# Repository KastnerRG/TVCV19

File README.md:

This software is Copyright © 2021 The Regents of the University of California. All Rights Reserved.

Permission to use, copy, modify, and distribute this software and its documentation for educational, research and non-profit purposes, without fee, and without a written agreement is hereby granted, provided that the above copyright notice, this paragraph and the following three paragraphs appear in all copies.

Permission to make commercial use of this software may be obtained by contacting:
Technology Transfer Office
9500 Gilman Drive, Mail Code 0910
University of California
La Jolla, CA 92093-0910
(858) 534-5815
invent@ucsd.edu

This software program and documentation are copyrighted by The Regents of the University of California. The software program and documentation are supplied "as is", without any accompanying services from The Regents. The Regents does not warrant that the operation of the program will be uninterrupted or error-free. The end-user understands that the program was developed for research purposes and is advised not to rely exclusively on the program for any reason.

IN NO EVENT SHALL THE UNIVERSITY OF CALIFORNIA BE LIABLE TO ANY PARTY FOR DIRECT, INDIRECT, SPECIAL, INCIDENTAL, OR CONSEQUENTIAL DAMAGES, INCLUDING LOST PROFITS, ARISING OUT OF THE USE OF THIS SOFTWARE AND ITS DOCUMENTATION, EVEN IF THE UNIVERSITY OF CALIFORNIA HAS BEEN ADVISED OF THE POSSIBILITY OF SUCH DAMAGE. THE UNIVERSITY OF CALIFORNIA SPECIFICALLY DISCLAIMS ANY WARRANTIES, INCLUDING, BUT NOT LIMITED TO, THE IMPLIED WARRANTIES OF MERCHANTABILITY AND FITNESS FOR A PARTICULAR PURPOSE. THE SOFTWARE PROVIDED HEREUNDER IS ON AN "AS IS" BASIS, AND THE UNIVERSITY OF CALIFORNIA HAS NO OBLIGATIONS TO PROVIDE MAINTENANCE, SUPPORT, UPDATES, ENHANCEMENTS, OR MODIFICATIONS.

# TVCV19

**MedECC** is an opensource telemedicine app to allow clinicians to better scale personnel resources.
Although hardware can be mass produced, clinician knowledge and experience cannot and this needs to be scaled out somehow.
Our platform aims to organize the heterogeneous hardware and manpower resources into a patient monitoring and decision making hierarchy.

If 10 COVID patients suddenly show up at a hospital with breathing difficulty, a misjudgement by the physician on who needs immediate intervention can be deadly. Our app allows caregivers to safely ration complex medical care to those who need it the most in order to save the most amount of lives.

This is how it works:

Traditionally, a bedside provider has to contact the physician via pager, a physician would then come to assess the patient at bedside, then put in orders before he/she can move onto the next patient.

The app provides instant access to a patient. A video feed along with real time patient data can be used by the supervising provider to assess a patient's condition. Once a decision is made, on the spot instructions can be given, or the supervisor can come prepared for a bedside procedure. This also means less exposure for doctors to infected patients, and less likely they’ll fall sick.

In cases where the supervising physician is overwhelmed or needs more complex help, the app allows quickly passing a patient to a specialist and ensures that cases are vetted before necessitating specialist attention.

You can learn more by browsing our [concept slides](https://docs.google.com/presentation/d/1jx_JJByAbFSXHXhZfbF9ar7q-Zx0MacvegpB00uDiNY/edit?usp=sharing) and listening to the accompanying [audio](https://www.uberconference.com/getmp3/AMIfv96b4tICKo7poclDD1wA3ljoQGVjX5lJ87UGyMusDsqpWrA9_SicAiTtTIgBCxpy7tUZsg8eZMD__9GbqGigc21ryxLr58KPmLOuIUcWgVltLQEmKRbjEPGKtYLqD_cy1Fx86Uls0aoCrx9p41Y52YWyEJF-Uw.mp3).

We are currently racing against the global novel coronavirus pandemic and could use a hand. 

If you want to contribute to the project, please fill out this [online form](https://docs.google.com/forms/d/e/1FAIpQLSf2osgKSobmYf0kSwzRrotV2hk5i8TjtZZdn5XptA1UjeIXVA/viewform)  and join our [slack channel](https://join.slack.com/t/scalablecv19solutions/shared_invite/zt-cxcbnbyu-yu4dxzaMjjnQvBGkQYVkxw) (#tv-cv19).

## How to Run
**Note:** If you have an old database created from the DB scripts, be sure to drop the DB before continuing.

### Setup the database for development
We use mySQL for our backend database.  The development instance uses a predetermined password.

To setup the database follow these steps:
1. Execute `ALTER USER 'root'@'localhost' IDENTIFIED BY 'Password1'` in mySQL
1. Execute `dotnet tool install --global dotnet-ef` to install the tools for Entity Framework.
1. Execute `dotnet ef database update` to create the database.

### Before running the C# Code
1. Navigate to `./frontend/TvCv19.Frontend/ClientApp`
1. Execute `npm install`
1. Execute `ng serve`.  **Note: You must be running `ng serve` for the ASP.Net Core web app to be able to display the website.**

### Run the C# Code
1. Launch `./frontend/TvCv19.Frontend.sln`
1. Run the app

## Add New Migrations
After updating the models or the `MedeccContext`, it is necessary to create a new DB migration.  To do so, execute `dotnet ef migrations add <migration name>`.

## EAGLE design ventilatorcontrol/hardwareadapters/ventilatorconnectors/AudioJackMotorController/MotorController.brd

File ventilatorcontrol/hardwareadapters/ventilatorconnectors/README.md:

# Hardware Adapters

**TVCV19** has a mobile phone user interface. It is therefore important to be able to control a ventilator from an unmodified phone. Our hardware adapters have a 3.5mm jack that plugs into phones to alow this. We provide sample designs for a microcontroller interface [here](AudioJackIO) as EAGLE projects. 

Eagle is free for non-commercial use, so the designs can be modified to suit available components. Note that our circuits are designed for the  following 4pin 3.5mm jack style. Some jacks (apple jacks) swap gnd and mic. Be sure to check.

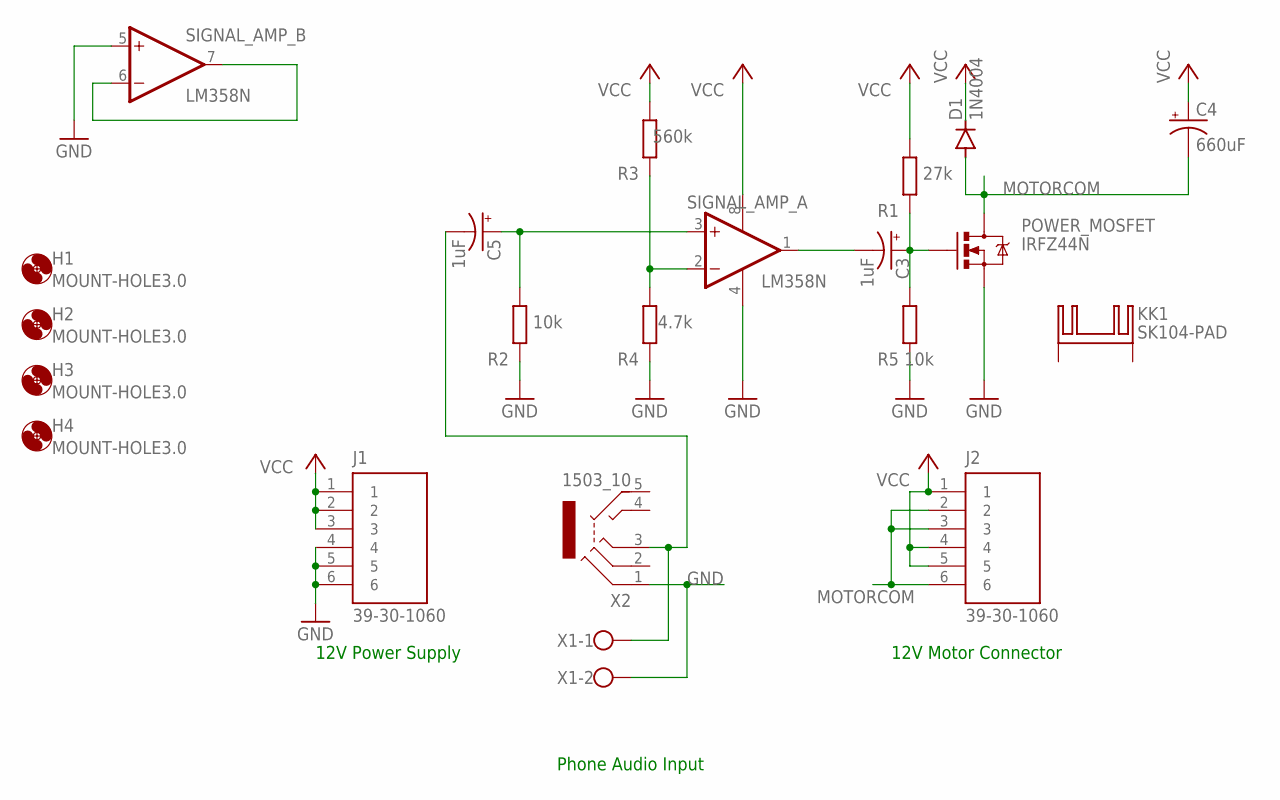
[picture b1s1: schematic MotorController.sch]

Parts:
C3, C5: 1uF; E2,5-7
C4: 660uF; E5-10,5
D1: 1N4004; DO41-10
H1, H2, H3, H4: MOUNT-HOLE3.0; 3,0
J1, J2: 39-30-1060; MOLEX_39-30-1060
KK1: SK104-PAD
POWER_MOSFET: IRFZ44N; TO-220
R1: 27k; 0204/7
R2, R5: 10k; 0204/7
R3: 560k; 0204/7
R4: 4.7k; 0204/7
SIGNAL_AMP_: LM358N; DIL08
X1: W237-102
X2: 1503_10

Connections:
GND: J1.4, J1.5, J1.6, POWER_MOSFET.3 (S), R2.1, R4.1, R5.1, SIGNAL_AMP_.4 (V-), SIGNAL_AMP_.5 (+IN), X1.2, X2.1
MOTORCOM: C4.-, D1.A, J2.2, J2.3, J2.6, POWER_MOSFET.2 (D)
unnamed: C5.+, R2.2, SIGNAL_AMP_.3 (+IN)
unnamed: R3.1, R4.2, SIGNAL_AMP_.2 (-IN)
unnamed: C3.-, SIGNAL_AMP_.1 (OUT)
unnamed: C3.+, POWER_MOSFET.1 (G), R1.1, R5.2
unnamed: SIGNAL_AMP_.6 (-IN), SIGNAL_AMP_.7 (OUT)
unnamed: C5.-, X1.1, X2.3
VCC: C4.+, D1.C, J1.1, J1.2, J1.3, J2.1, J2.4, J2.5, R1.2, R3.2, SIGNAL_AMP_.8 (V+)

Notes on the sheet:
Phone Audio Input
12V Motor Connector
12V Power Supply

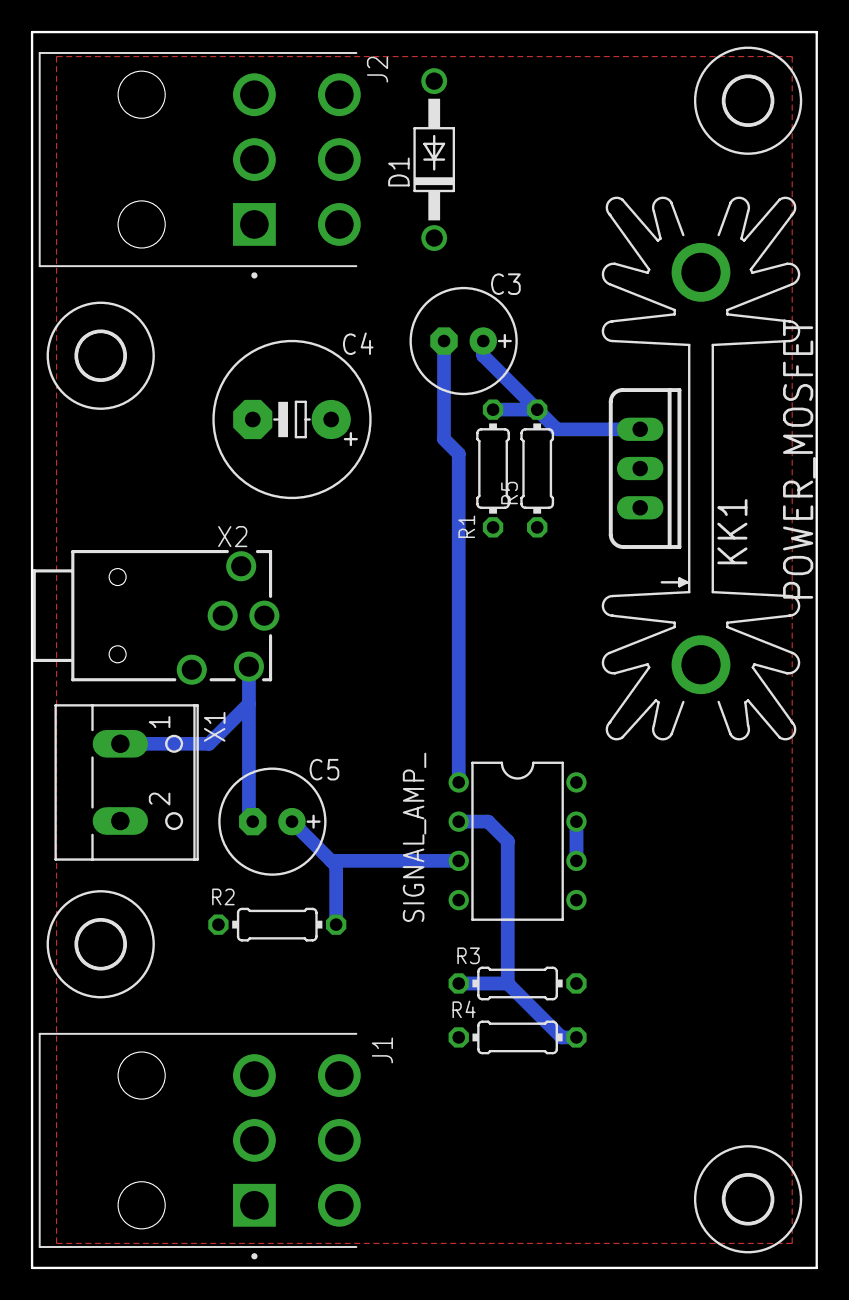
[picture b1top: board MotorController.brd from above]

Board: 2 copper layers, 50.8 x 80.0 mm, 20 parts (0 on the bottom side), 9 nets.

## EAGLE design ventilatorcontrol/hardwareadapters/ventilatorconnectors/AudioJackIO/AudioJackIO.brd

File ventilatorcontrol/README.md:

# Ventilator Control

**TV CV19** has remote control features for ventilators. Our goal is that skilled caregivers can more efficiently manage cases in times of crisis.
Ventilator control works using the audio jack of a smart phone to talk to the ventilator. This allows a patient's own phone to be used to remotely manage their case without any need for expensive computer equipment purchases.

A simple circuit needs to be built to control most ventilators, although we hope open source ventilators teams will consider building in support. The mobile app is [here](/mobileapp). If your ventilator does not have an audio jack, you can find example ventilator connectors [here](hardwareadapters/ventilatorconnectors). If you are an open source ventilator team that would like to add support for our interface, an example controller is [here](hardwareadapters/ventilatorcontrollers)

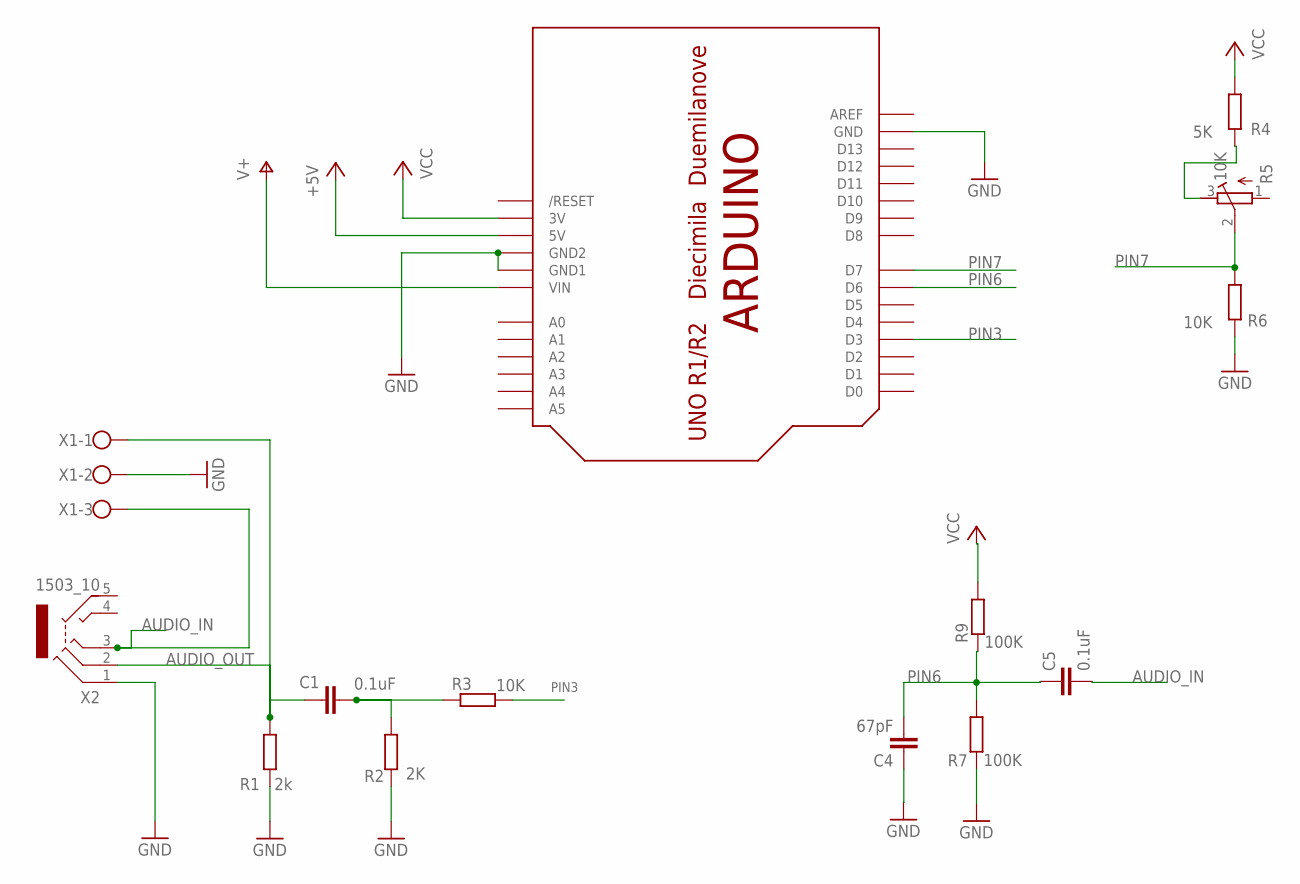
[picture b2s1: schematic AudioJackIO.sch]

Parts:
C1, C5: 0.1uF; C025-025X050
C4: 67pF; C025-025X050
R1: 2k; 0204/7
R2: 2K; 0204/7
R3, R6: 10K; 0204/7
R4: 5K; 0204/7
R5: 10K; RTRIM64Y
R7, R9: 100K; 0204/7
U$1: ARDUINO-BPLACE
X1: W237-103
X2: 1503_10

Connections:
+5V: U$1.5V
AUDIO_IN: C5.2, X1.3, X2.3
AUDIO_OUT: C1.1, R1.2, X1.1, X2.2
GND: C4.1, R1.1, R2.2, R6.1, R7.1, U$1.GND, U$1.GND1, U$1.GND2, X1.2, X2.1
unnamed: C1.2, R2.1, R3.1
unnamed: R4.1, R5.3 (E)
PIN3: R3.2, U$1.D3
PIN6: C4.2, C5.1, R7.2, R9.1, U$1.D6
PIN7: R5.2 (S), R6.2, U$1.D7
V+: U$1.VIN
VCC: R4.2, R9.2, U$1.3V

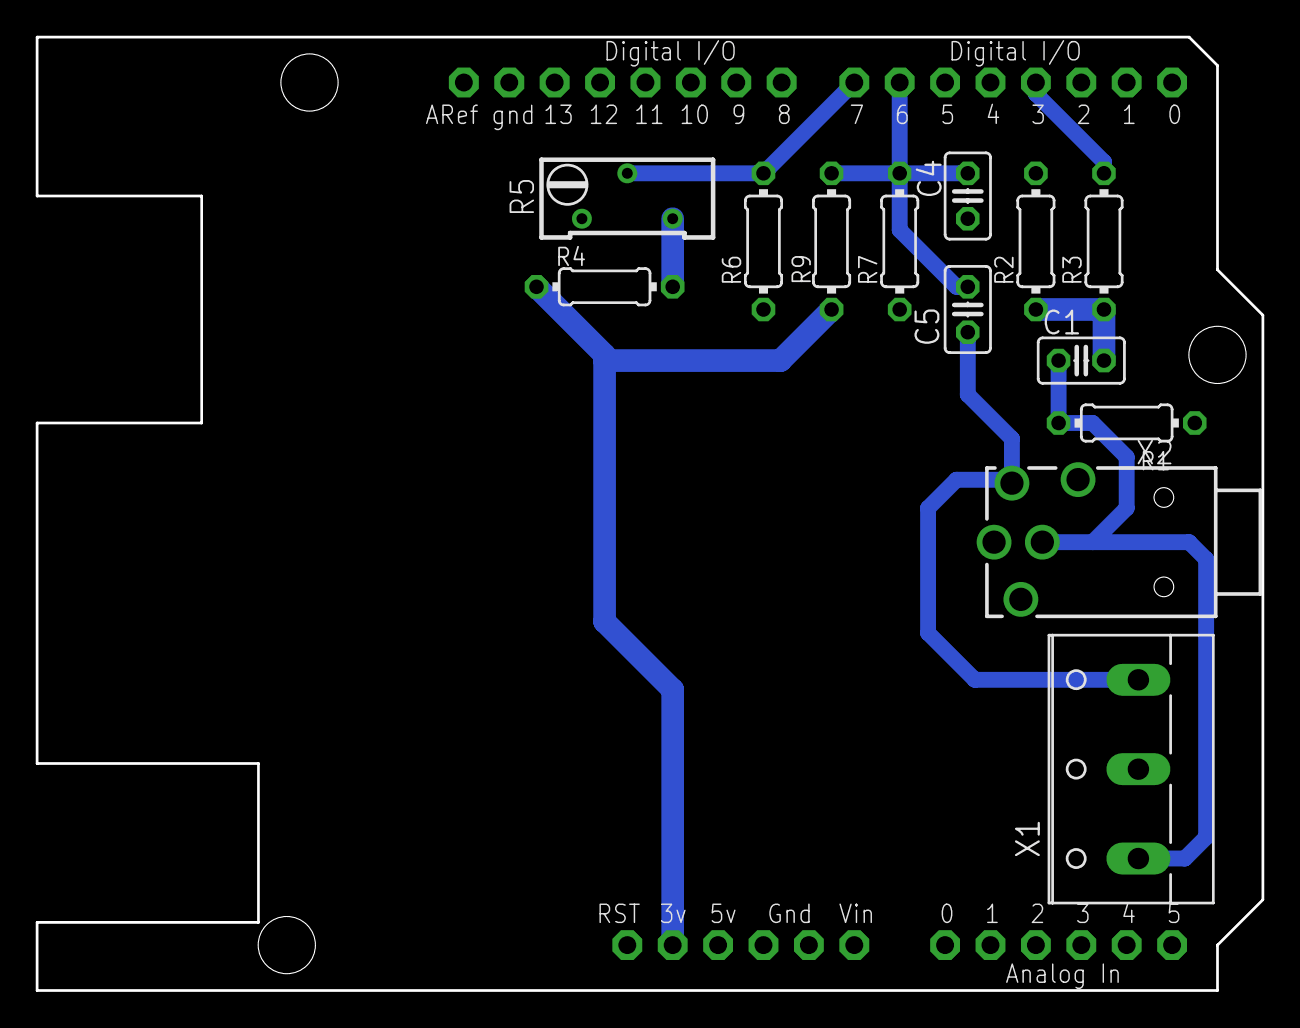
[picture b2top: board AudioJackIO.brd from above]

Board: 2 copper layers, 68.6 x 53.3 mm, 14 parts (0 on the bottom side), 9 nets.

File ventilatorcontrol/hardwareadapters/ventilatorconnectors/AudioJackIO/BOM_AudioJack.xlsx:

Part | Value | Device | Package | Description | MPN | OC_FARNELL
C1 | 0.1uF | C-EU025-025X050 | C025-025X050 | CAPACITOR, European symbol | SR201C104KARTR1 | 2332963
C4 | 67pF | C-EU025-025X050 | C025-025X050 | CAPACITOR, European symbol | SR151A680JAR | 2332952
C5 | 0.1uF | C-EU025-025X050 | C025-025X050 | CAPACITOR, European symbol | SR201C104KARTR1 | 2332963
R1 | 2k | R-EU_0204/7 | 0204/7 | RESISTOR, European symbol | MCRC1/4G202JT-RH | 1133381
R2 | 2K | R-EU_0204/7 | 0204/7 | RESISTOR, European symbol | MCRC1/4G202JT-RH | 1133381
R3 | 10K | R-EU_0204/7 | 0204/7 | RESISTOR, European symbol | MCRC1/4G103JT-RH | 1133371
R4 | 5K | R-EU_0204/7 | 0204/7 | RESISTOR, European symbol | MCRC1/4G472JT-RH | 1133396
R5 | 10K | R-TRIMM64Y | RTRIM64Y | Trimm resistor | 67YR10KLF | 1304530
R6 | 10K | R-EU_0204/7 | 0204/7 | RESISTOR, European symbol | MCRC1/4G103JT-RH | 1133371
R7 | 100K | R-EU_0204/7 | 0204/7 | RESISTOR, European symbol | MCRC1/4G104JT-RH | 1133372
R9 | 100K | R-EU_0204/7 | 0204/7 | RESISTOR, European symbol | MCRC1/4G104JT-RH | 1133372
X1 |  | W237-103 | W237-103 | WAGO SCREW CLAMP | 1729131 | 3041451
X2 | 1503_10 | 1503_10 | 1503_10 | Jack connectors according to JISC 6560, 3.5 mm | 1503 10 | 1308868

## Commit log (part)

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2020-03-26 initial landing page
2020-03-26 fixed bugs
2020-04-01 initial checkin of frontend
2020-04-01 fixes for docker container
2020-04-03 chat ui
2020-04-04 merged
2020-04-04 further work towards accurate ui
2020-04-04 Beginning of the front end (#1)
2020-04-04 remove .vs
2020-04-04 more ui work
2020-04-05 chatting works
2020-04-05 Feature/navigation (#2)
2020-04-05 refactored flow so like mocks
2020-04-05 Patient registration (#3)
    * Refactored ui so more inline with mocks
2020-04-05 fix build
2020-04-05 physician repository
2020-04-05 fixed issues from PR
2020-04-05 fixed broken build
2020-04-05 beginning refactored firstline component into heirachy component that show reports deleting duplicate code
2020-04-05 Physician heirachy (#6)
    * beginning refactored firstline component into heirachy component that show reports deleting duplicate code
    * last push :(
2020-04-05 demo prep
2020-04-07 template library and demo sketch of 'AudioIO' for ventilator control
2020-04-07 sensor names and command string format example in AudioIO.h
2020-04-07 Fix in modem variable visibility
2020-04-08 updated class template in library
2020-04-08 API working but strange bug in 'parseCommand' that causes crash and reboot. Unsure why
2020-04-08 Added Debug Interface for Decoder
2020-04-09 Eagle schematic for interface circuit. Needs a PCB layout done
2020-04-09 enq-ack handshake apk
2020-04-10 daily co work
2020-04-10 created shared module that exports all common modules split out shared componenets and services moved patient registration to patient project
2020-04-10 Initial patient list work (#7)
    * Finished Caregiver registration
    * Created list view and initial work for patient component
    * created shared module that exports all common modules
    split out shared componenets and services
    moved patient registration to patient project
2020-04-10 retactored api routes hooked up assign caregiver to registered physicians
2020-04-10 retactored api routes (#8)
    hooked up assign caregiver to registered physicians
2020-04-10 begininig patient detail component
2020-04-11 added audio to motor control circuit
2020-04-11 Styled as close to mock added name and date to the message
2020-04-12 fix dailyco api
2020-04-12 create projects for routes
2020-04-12 fixed build
2020-04-12 Fixed build and patient list styling (#11)
2020-04-12 added change shift component
2020-04-12 heirachy componenet getting data from services removing messages from Physician model deleting duplicate controller
2020-04-12 persiting message data removing duplicate service
2020-04-12 big refactor. still more to come
2020-04-13 hooked up admin route
2020-04-13 moved missing methods into shared service deleted duplicate service
2020-04-13 Updated Handshake/FSK Thread Priority
2020-04-14 created the physician/messaging/checklist branch
2020-04-14 trying out the physician messagning checklist forms
2020-04-14 added the skleton for physician messaging checklist, no functionality
2020-04-14 two way comms between phone + Arduino. phone reads knobs not data. BUG BUG. Arduino numerical values are garbage on modem but ok on serial port. Fix.
2020-04-14 control knob phone<->arduino working
2020-04-17 Updated PCM Waveform Generator
2020-04-17 boilerplate JSON and broken PCM
2020-04-17 one project per route. This should help with org
2020-04-17 physician hierarchy for caregiver and physician
2020-04-17 patient flow complete
2020-04-17 button for patient in heirarchy
2020-04-17 layout changes
2020-04-17 added dummy ventilator readouts display
2020-04-17 continue to build out flows'
2020-04-18 voice recording with persitance (#14)
2020-04-18 Added JSON parser. BUGS! 1) the JSON can be fragmented into several SOFT MODEM buffers. We miss some key value pairs in this case. 2) runonui crases for ventilator readouts (line 389). No idea why
2020-04-18 Image upload from chat
    *Refactored audio controllers services and repos to be media so can share the same logic for all media types (image and audio).
    *Image upload functionality and styling.
    *Fixed bug with multiple recordings getting uploaded and frontend build
2020-04-20 Adjusted PCM Waveform Frequency Range
2020-04-21 fix a couple of bugs from reorg
2020-04-21 can get to all pages
2020-04-22 broken wave
2020-04-25 got messaging working
2020-04-25 changed filename for audio added basic frontend caching for audio files
2020-04-25 hooked up shift change for patient
2020-04-26 fix build errors
2020-04-26 created dialog for adding respirator stats
2020-04-26 displaying and persisting resprirator stats
2020-04-26 built out logic for physician messanging checklist
2020-04-26 hooked up shift change again
2020-04-26 hooked up shift change again (#19)
2020-04-27 first pass at broadcasting from patient (#20)
2020-04-28 updated naming to MedECC on splash page
2020-04-28 Old Opamp motor controller schematic removed and Motorcontroller folder renamed.
2020-04-28 uController AudioJack interface schematic and layout. Added an alternative connector in parallel to the audio jack and gerber file exported for a small and standard arduino shield.
2020-05-01 basic example of Raspberry pi to phone communication using an Arduino bridge
2020-05-01 added untracked files from last commit for physicians messaging checklist
2020-05-02 deleted comment in physician message checklist
2020-05-03 styling registration forms and deleted unused patient component
2020-05-05 added scheduleInterval to checklist model
2020-05-07 added and tested double buffers for writing to ventilator readout registers. Only works if writing is Mutex to one bus agent of the two, otherwise race conditions are possible.
2020-05-07 verified SPI JSON IO works and made better able to handle command register extensions
2020-05-08 supervisor on caregiver registration
2020-05-08 Getting patients for supervisors
2020-05-08 Fixed Bug in PCM Mode
2020-05-08 hooking up shift changes for physicians
2020-05-08 shift changes for physicians (#24)
2020-05-09 updated patient detail to have new logos from figma (#25)
    fixed spelling mistake in hierarchy
    added supervisor to hierarchy screen
2020-05-10 initial work to notify physicians and bedside caregivers when they get a message in real time
2020-05-11 cordova build
2020-05-11 Fixed Packet Fragmentation and Handshake Thread Taking Over Bus
2020-05-12 fixed android app to look for the same terminator that Arduino issues
2020-05-16 small tidy
2020-05-22 Implemented GUID for patient ID. Full GUID is too long for daily.co name - used first 20 characters and removed 'patient-' prefix to make shorter.
2020-05-22 fixed typo
2020-05-26 Made small update to GUID as patient ID
2020-05-30 hooking up commander
2020-05-30 hooking up commander (#30)
2020-05-30 added additional subnet and nginx ingress controller
2020-05-30 Terraform and kubernetes (#31)
    * scripting up vpc creation and kube cluster deployment for web app
    * added additional subnet and nginx ingress controller
2020-05-31 fixed header and footer (#33)
2020-05-31 unneeded pdb selector
2020-06-04 add SPI and ARTe features to IO controller
2020-06-05 Add menu button and patient-menu Add menu toggle
2020-06-05 Add patient-qr routing
2020-06-05 Add toolbar show() & hide() methods
2020-06-05 Added patient-qr component
2020-06-07 hierarchy v2 and styling tweaks (#36)
2020-06-07 Fixed patient-menu toggle, added styling
2020-06-19 using http client factory and adding token to patient
2020-06-24 added hierarchy
2020-06-24 mysql repo implementation small bug fixes
2020-07-04 latest angular 9
2020-07-04 latest angular material
2020-07-05 deafult admin user
2020-07-05 login mostly working
2020-07-11 fix null reference
2020-07-14 mysql repo implementation
2020-07-16 added mySQL credentials for UCSD Free Clinic Deployment
2020-07-17 using http client factory and adding token to patient
    escalation working for bedside and physician
    saving notifications server side
    delete all patients
2020-07-17 patient escalation and notification tweaks #39
2020-07-21 add log out functionality
2020-07-22 switch to using jwt token to support alternative login
2020-07-23 add mat list
2020-07-23 user management ui
2020-07-23 Added tables for patients and physicians, added dischargePatient method in patient.service.ts, added empty first option for dropdowns
2020-07-24 finished buttons and routes for nurses doctors menu
    cosmetic updates to nurses doctors menu
    added route for QR code for Nurse&doctors menu
    added QR codes for nurses doctors menu
    added changes from pull request as well as age in patient-registration
    implemented age for patient registration
    cosmetic name changes for carer-menu.component
2020-07-24 using a drawer
2020-07-27 slide in nurses doctors menu (#27)
2020-07-27 updated to with refactored code
    created the physician/messaging/checklist branch
    trying out the physician messagning checklist forms
    added the skleton for physician messaging checklist, no functionality
    for physician messaging checklist, added a button listener
    built out logic for physician messanging checklist
    added untracked files from last commit for physicians messaging checklist
2020-07-27 Feature/physician checklist (#35)
2020-08-06 add entity framework to handle automatic migrations
2020-08-09 added note to readme
2020-08-09 add roles
2020-08-09 add patient role
2020-08-10 added authorization
2020-08-10 switch to using int ids. This is to work around a bug that we are running into with mysql indexes
2020-08-10 roles are finished
2020-08-13 auto gen database
2020-08-15 added form fields to capture username and password
    updating username and password hash during patient admission process
2020-08-15 tidy up and fixed error
2020-08-22 Revert "fixed some bugs in entity framework"
    This reverts commit 17cd80a3f37fb895ca64525d416ea38009e2e4e9.
2020-08-22 Revert "Merge pull request #41 from KastnerRG/feature/entity-core"
    This reverts commit 28d4fcd311bceae234f60847798ce235e8c39b9a, reversing
    changes made to 3ab622d617b3fb36158e8935af469242ab50a03b.
2020-08-30 reverted entity framework commits
    removed redundent angular projects
    consolidated share caregiver to caregiver
    re implemented registration and authorization
2020-08-31 fixed authorization on signal r fixed menu routes
2020-08-31 changed folder structure
2020-09-06 added admin table
2020-09-06 extra fields for patient details hooked up chrome push db
2021-05-08 Bump ng-packagr in /frontend/TvCv19.Frontend/ClientApp
    Bumps [ng-packagr](https://github.com/ng-packagr/ng-packagr) from 9.1.1 to 10.1.1.
    - [Release notes](https://github.com/ng-packagr/ng-packagr/releases)
    - [Changelog](https://github.com/ng-packagr/ng-packagr/blob/master/CHANGELOG.md)
    - [Commits](https://github.com/ng-packagr/ng-packagr/compare/v9.1.1...v10.1.1)
2021-07-17 added PCB manufacturing files
2021-08-25 Bump Microsoft.AspNetCore.Authentication.JwtBearer
    Bumps [Microsoft.AspNetCore.Authentication.JwtBearer](https://github.com/aspnet/AspNetCore) from 3.1.6 to 3.1.18.
    - [Release notes](https://github.com/aspnet/AspNetCore/releases)
    - [Commits](https://github.com/aspnet/AspNetCore/compare/v3.1.6...v3.1.18)
    ---
    updated-dependencies:
    - dependency-name: Microsoft.AspNetCore.Authentication.JwtBearer
2022-02-11 Bump karma from 4.4.1 to 6.3.14 in /frontend/TvCv19.Frontend/ClientApp
    Bumps [karma](https://github.com/karma-runner/karma) from 4.4.1 to 6.3.14.
    - [Release notes](https://github.com/karma-runner/karma/releases)
    - [Changelog](https://github.com/karma-runner/karma/blob/master/CHANGELOG.md)
    - [Commits](https://github.com/karma-runner/karma/compare/v4.4.1...v6.3.14)
    ---
    updated-dependencies:
